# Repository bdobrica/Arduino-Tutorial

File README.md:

This is a small tutorial for Arduino programming, intended to be used by physicists in their work. The tutorial steps are ordered and should be followed in the given order. This is also the basis for a future lecture I will teach at Faculty of Physics, University of Bucharest for Renewable and Alternative Energy Sources Master Programme.

--
Bogdan D.

The content of this repository is provided "as is" with no implied warranty. Also the content is available under [Attribution-NonCommercial-NoDerivatives 4.0 International](https://creativecommons.org/licenses/by-nc-nd/4.0/legalcode).

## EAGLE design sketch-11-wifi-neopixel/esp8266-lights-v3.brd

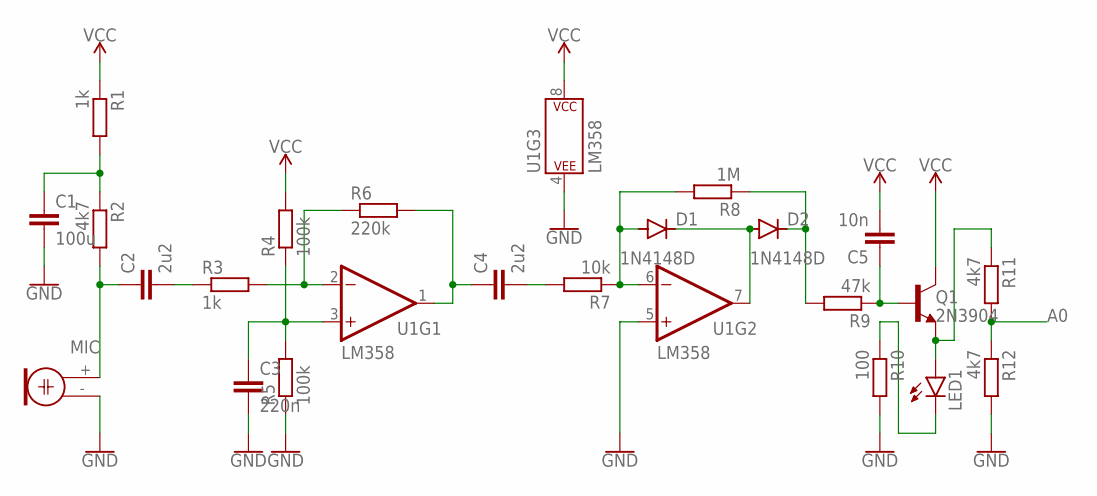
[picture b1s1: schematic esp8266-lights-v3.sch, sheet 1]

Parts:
C1: 100u; C050-024X044
C2, C4: 2u2; C050-024X044
C3: 220n; C050-024X044
C5: 10n; C050-024X044
D1, D2: 1N4148D; DO35-10
LED1: LED5MM
MIC: ELECTRET; 9.7ELECTRET
Q1: 2N3904; TO92
R1, R3: 1k; 0309/10
R2, R11, R12: 4k7; 0309/10
R4, R5: 100k; 0309/10
R6: 220k; 0309/10
R7: 10k; 0309/10
R8: 1M; 0309/10
R9: 47k; 0309/10
R10: 100; 0309/10
U1: LM358; DIP08-KIT

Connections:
A0: R11.2, R12.1; also elsewhere on the board
GND: C1.2, C3.2, MIC.- (1), R5.1, R10.2, R12.2, U1.4 (P$V-), U1.5 (+IN); also elsewhere on the board
unnamed: C2.1, MIC.+ (2), R2.2
unnamed: C1.1, R1.2, R2.1
unnamed: C2.2, R3.1
unnamed: C3.1, R4.1, R5.2, U1.3 (+IN)
unnamed: R3.2, R6.1, U1.2 (-IN)
unnamed: C4.1, R6.2, U1.1 (OUT)
unnamed: C4.2, R7.2
unnamed: D1.C, D2.A, U1.7 (OUT)
unnamed: D1.A, R7.1, R8.2, U1.6 (-IN)
unnamed: D2.C, R8.1, R9.2
unnamed: C5.1, Q1.2 (B), R9.1
unnamed: LED1.K (C), R10.1
unnamed: LED1.A, Q1.3 (E), R11.1
VCC: C5.2, Q1.1 (C), R1.1, R4.2, U1.8 (P$V+); also elsewhere on the board

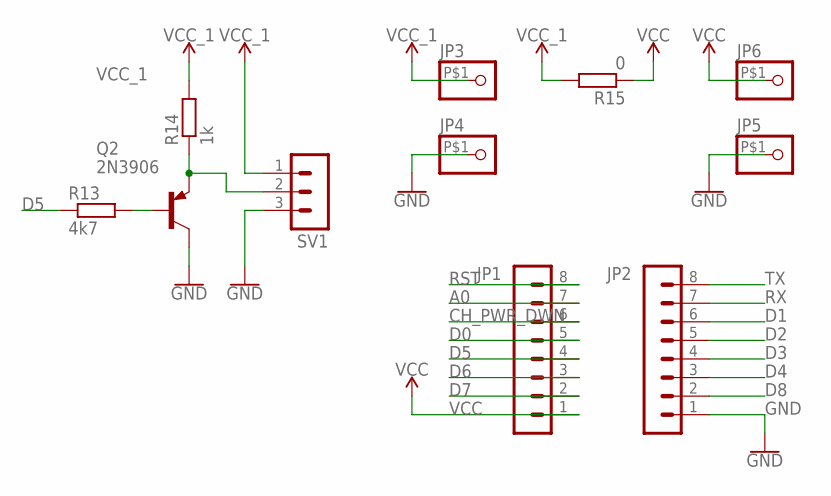
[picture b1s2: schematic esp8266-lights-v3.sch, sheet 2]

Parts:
JP1, JP2: MA08-1
JP3, JP4, JP5, JP6: PINHD-1X1-BIGPOGO; 1X1-BIGPOGO
Q2: 2N3906; TO92
R13: 4k7; 0309/10
R14: 1k; 0309/10
R15: 0; 0309/10
SV1: MA03-1

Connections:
A0: JP1.7; also elsewhere on the board
CH_PWR_DWN: JP1.6
D0: JP1.5
D1: JP2.6
D2: JP2.5
D3: JP2.4
D4: JP2.3
D5: JP1.4, R13.1
D6: JP1.3
D7: JP1.2
D8: JP2.2
GND: JP2.1, JP4.P$1, JP5.P$1, Q2.1 (C), SV1.3; also elsewhere on the board
unnamed: Q2.2 (B), R13.2
unnamed: Q2.3 (E), R14.1, SV1.2
RST: JP1.8
RX: JP2.7
TX: JP2.8
VCC: JP1.1, JP6.P$1, R15.1; also elsewhere on the board
VCC_1: JP3.P$1, R14.2, R15.2, SV1.1

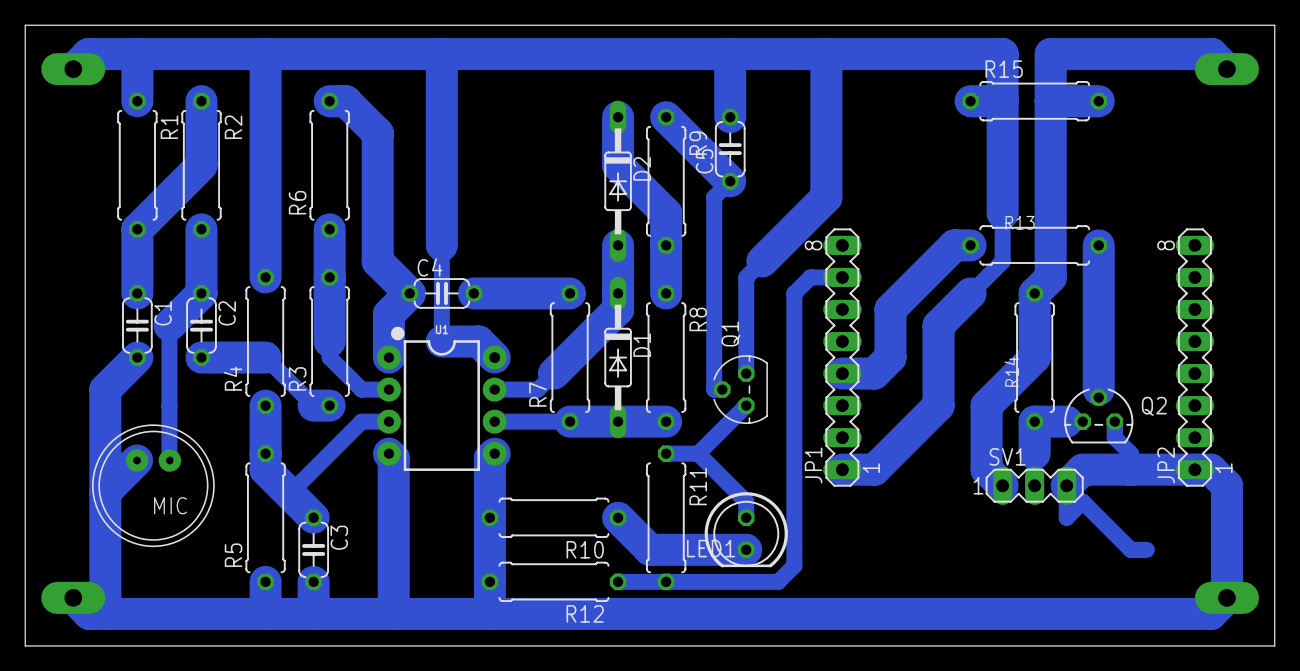
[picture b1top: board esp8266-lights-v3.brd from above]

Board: 2 copper layers, 99.0 x 49.2 mm, 34 parts (0 on the bottom side), 20 nets.

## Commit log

2016-07-09 :neckbeard: Added .gitattributes & .gitignore files
2016-07-09 1st Commit
    Added a blinking LEDs sketch.
2016-07-11 Other Sketches and 1st Python Code
    Added a few other sketches and moved to communication with the computer.
    For this, the 4th sketch is the most advanced.
2016-07-11 Forgot about ReadMe
    Added a ReadMe.md file.
2017-04-09 Updates for Lectures (Spring 2017)
    Implementing the "Very Low Costs Environmental Sensors".
2017-05-06 Measuring units.
    Added measuring units to charts and helper functions to get conductivity
    and current/voltage from raw data.
2017-05-20 8th Lecture
    Hotwire anemometer with only a lightbulb and a resistor.
2018-03-19 Improvements
    - added fritzing schematics;
    - added octave oscilloscope;
    - added switching power supply model;
2020-01-12 Round Robot Wi-Fi ESP8266 Sketches
    - v1: just testing the wi-fi connection;
    - v2: test the http server;
    - v3: add the motor controlling code
    - v4: add the http commands handler
    - final: add a html5 interface, to allow mobile phone control;
    - interface: the html5 interface code;
2020-01-25 NeoPixel WiFi Project
    A small project creating music driven neopixel leds. Here are the schematics and the sketches. Use the final for the final version.
2020-01-26 Some PDF Files
    - with schematics;
    - with component placement;
    - ready to print mask;

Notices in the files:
parts and their libraries:
SparkFun-IC-Amplifiers: Licensing: Creative Commons ShareAlike 4.0 International - https://creativecommons.org/licenses/by-sa/4.0
